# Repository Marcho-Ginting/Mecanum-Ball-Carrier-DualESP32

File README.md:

# Mecanum-Ball-Carrier-DualESP32

A high-performance mechatronic system utilizing omnidirectional locomotion and a distributed processing architecture for precision robotics tasks.

## 📊 Technical Specifications
* **Architecture:** Dual-ESP32 System (Distributed processing for control and feedback).
* **Locomotion:** 4-wheel drive using Mecanum wheels for 360-degree holonomic movement.
* **Actuation:** 4x High-torque Direct Drive actuators with integrated encoders.
* **PCB:** Custom-manufactured board for power distribution and encoder signal conditioning.

## ⚡ Engineering Highlights
* **Distributed Processing:** Implemented a Dual-ESP32 architecture to isolate real-time motor control and encoder processing from higher-level telemetry and communication, ensuring system stability.
* **Precision Motion Control:** Developed algorithms for Mecanum wheel kinematics, utilizing closed-loop encoder feedback to achieve high-precision velocity and positional tracking.
* **System Integration:** Engineered a custom PCB to consolidate four motor drivers and encoder inputs, optimizing signal integrity and reducing the mechanical footprint of the electronics.
* **Leadership:** Led a cross-disciplinary team of engineers, managing the full development lifecycle from component selection to final system debugging.

## 📂 Repository Structure
* `/logic`: Main logic digital board
* `/pdb`: Driver motor and power distribution board.

## 📷 3D KiCad Render Images

<table style="width:100%">
  <tr>
    <td align="center">
      <br/>
      <b>PDB</b>
    </td>
    <td align="center">
      <br/>
      <b>Logic</b>
    </td>
  </tr>
</table>

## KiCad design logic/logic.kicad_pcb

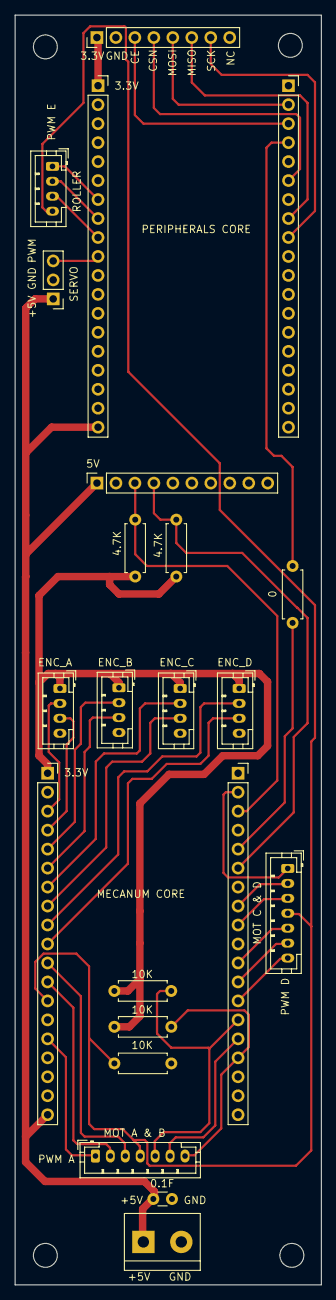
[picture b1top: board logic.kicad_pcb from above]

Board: 2 copper layers, 41.0 x 170.0 mm, 22 parts (0 on the bottom side), 38 nets.

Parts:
C_BYPASS1: 0.1uF; C_Disc_D3.0mm_W1.6mm_P2.50mm
J_DRV_SIG1, J_DRV_SIG2: Conn_01x07; JST_PH_B7B-PH-K_1x07_P2.00mm_Vertical
J_DRV_SIG_1: Conn_01x04; JST_PH_B4B-PH-K_1x04_P2.00mm_Vertical
J_IMU1: Conn_01x10_Socket; PinSocket_1x10_P2.54mm_Vertical
J_LEFT_ENC1, J_LEFT_ENC2: Conn_01x04; JST_PH_B4B-PH-K_1x04_P2.00mm_Vertical
J_LEFT_HEADERS1, J_LEFT_HEADERS2: Conn_01x19_Pin; PinSocket_1x19_P2.54mm_Vertical
J_LOGIC1: Screw_Terminal_01x02; TerminalBlock_bornier-2_P5.08mm
J_RF1: Conn_01x08_Pin; PinHeader_1x08_P2.54mm_Vertical
J_RIGHT_ENC1, J_RIGHT_ENC2: Conn_01x04; JST_PH_B4B-PH-K_1x04_P2.00mm_Vertical
J_RIGHT_HEADERS1, J_RIGHT_HEADERS2: Conn_01x19_Pin; PinSocket_1x19_P2.54mm_Vertical
J_SERVO1: Conn_01x03_Pin; PinHeader_1x03_P2.54mm_Vertical
R_JUMPER1: 0; R_Axial_DIN0207_L6.3mm_D2.5mm_P7.62mm_Horizontal
R_PULLUP1, R_PULLUP2: 4.7K; R_Axial_DIN0207_L6.3mm_D2.5mm_P7.62mm_Horizontal
R_PULLUP3, R_PULLUP4, R_PULLUP5: 10K; R_Axial_DIN0207_L6.3mm_D2.5mm_P7.62mm_Horizontal

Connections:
/3.3V_MEC: J_LEFT_ENC1.1, J_LEFT_ENC2.1, J_LEFT_HEADERS1.1, J_RIGHT_ENC1.1, J_RIGHT_ENC2.1, R_PULLUP1.2, R_PULLUP2.2, R_PULLUP3.2, R_PULLUP5.2
/3.3V_PER: J_LEFT_HEADERS2.1, J_RF1.1
/+5V: C_BYPASS1.1, J_IMU1.1, J_LEFT_HEADERS1.19, J_LEFT_HEADERS2.19, J_LOGIC1.1, J_SERVO1.1
/CE: J_RF1.3, J_RIGHT_HEADERS2.3
/CSN: J_RF1.4, J_RIGHT_HEADERS2.6
/ENC_A1: J_LEFT_ENC1.2, J_LEFT_HEADERS1.3
/ENC_A2: J_LEFT_ENC1.3, J_LEFT_HEADERS1.4
/ENC_B1: J_LEFT_ENC2.2, J_LEFT_HEADERS1.5
/ENC_B2: J_LEFT_ENC2.3, J_LEFT_HEADERS1.6
/ENC_C1: J_LEFT_HEADERS1.7, J_RIGHT_ENC1.2
/ENC_C2: J_LEFT_HEADERS1.8, J_RIGHT_ENC1.3
/ENC_D1: J_LEFT_HEADERS1.9, J_RIGHT_ENC2.2
/ENC_D2: J_LEFT_HEADERS1.10, J_RIGHT_ENC2.3
/GND_LOGIC: C_BYPASS1.2, J_IMU1.2, J_LEFT_ENC1.4, J_LEFT_ENC2.4, J_LEFT_HEADERS1.14, J_LEFT_HEADERS2.14, J_LOGIC1.2, J_RF1.2, J_RIGHT_ENC1.4, J_RIGHT_ENC2.4, J_RIGHT_HEADERS1.1, J_RIGHT_HEADERS2.1, J_SERVO1.2, R_PULLUP4.2
/IN_A1: J_DRV_SIG1.3, J_LEFT_HEADERS1.11
/IN_A2: J_DRV_SIG1.2, J_LEFT_HEADERS1.12
/IN_B1: J_DRV_SIG1.5, J_RIGHT_HEADERS1.14, R_PULLUP3.1
/IN_B2: J_DRV_SIG1.6, J_RIGHT_HEADERS1.15
/IN_C1: J_DRV_SIG2.3, J_RIGHT_HEADERS1.9
/IN_C2: J_DRV_SIG2.2, J_RIGHT_HEADERS1.8
/IN_D1: J_DRV_SIG2.5, J_RIGHT_HEADERS1.11
/IN_D2: J_DRV_SIG2.6, J_RIGHT_HEADERS1.12
/IN_E1: J_DRV_SIG_1.3, J_LEFT_HEADERS2.9
/IN_E2: J_DRV_SIG_1.2, J_LEFT_HEADERS2.8
/MISO: J_RF1.6, J_RIGHT_HEADERS2.8
/MOSI: J_RF1.5, J_RIGHT_HEADERS2.2
/PWM_A: J_DRV_SIG1.1, J_LEFT_HEADERS1.15
/PWM_B: J_DRV_SIG1.7, J_RIGHT_HEADERS1.16, R_PULLUP5.1
/PWM_C: J_DRV_SIG2.1, J_RIGHT_HEADERS1.2
/PWM_D: J_DRV_SIG2.7, J_RIGHT_HEADERS1.13
/PWM_E: J_DRV_SIG_1.1, J_LEFT_HEADERS2.7
/PWM_SERVO: J_LEFT_HEADERS2.10, J_SERVO1.3
/SCK: J_RF1.7, J_RIGHT_HEADERS2.9
/SCL: J_IMU1.3, J_RIGHT_HEADERS1.3, R_PULLUP2.1
/SDA: J_IMU1.4, J_RIGHT_HEADERS1.6, R_PULLUP1.1
/STBY: J_DRV_SIG1.4, J_DRV_SIG2.4, J_DRV_SIG_1.4, J_LEFT_HEADERS1.13, R_PULLUP4.1
/UART_MASTER: J_RIGHT_HEADERS2.4, R_JUMPER1.1
/UART_SLAVE: J_RIGHT_HEADERS1.5, R_JUMPER1.2

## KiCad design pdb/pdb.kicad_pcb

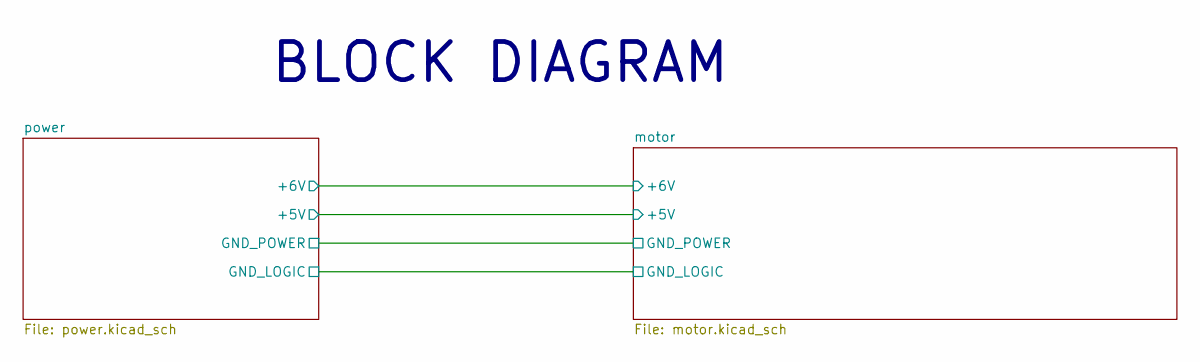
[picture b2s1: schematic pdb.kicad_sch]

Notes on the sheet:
BLOCK DIAGRAM

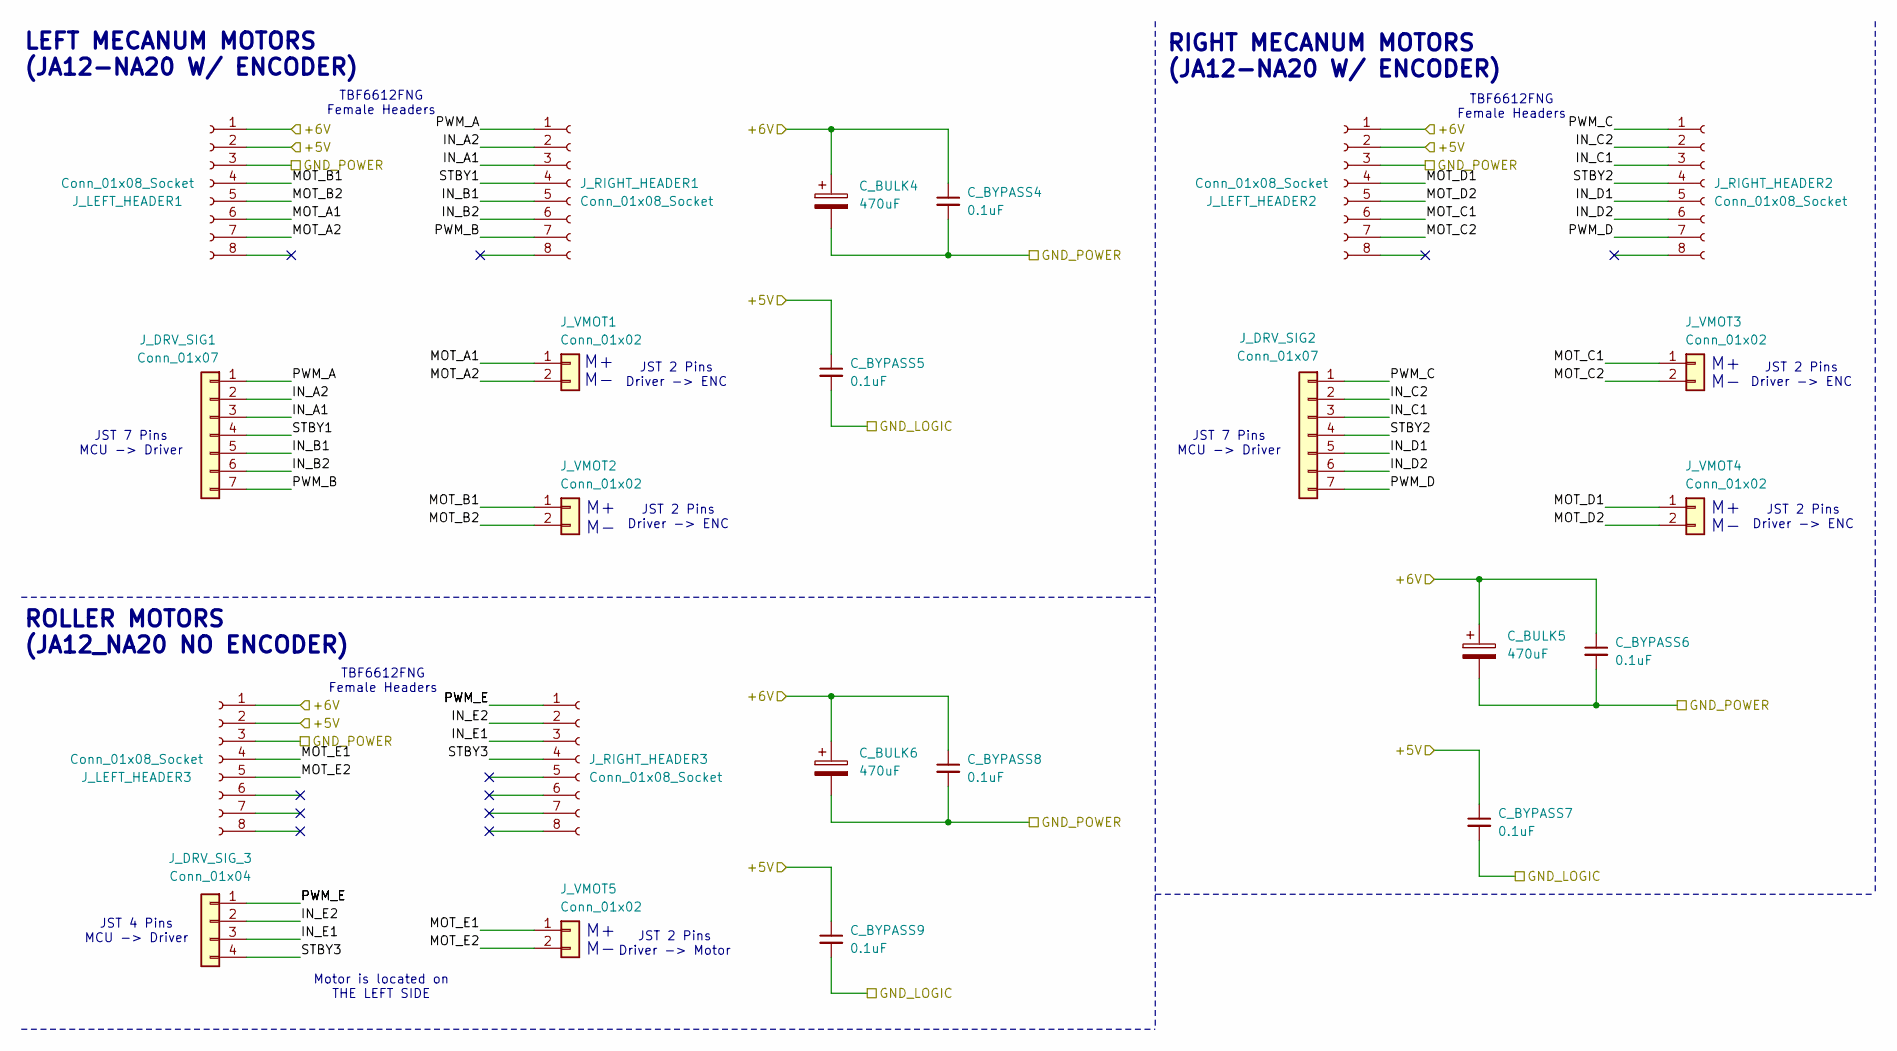
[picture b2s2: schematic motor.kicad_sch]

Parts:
C_BULK4, C_BULK5, C_BULK6: 470uF; CP_Radial_D10.0mm_P5.00mm
C_BYPASS4, C_BYPASS5, C_BYPASS6, C_BYPASS7, C_BYPASS8, C_BYPASS9: 0.1uF; C_Disc_D3.0mm_W1.6mm_P2.50mm
J_DRV_SIG1, J_DRV_SIG2: Conn_01x07; JST_PH_B7B-PH-K_1x07_P2.00mm_Vertical
J_DRV_SIG_3: Conn_01x04; JST_PH_B4B-PH-K_1x04_P2.00mm_Vertical
J_LEFT_HEADER1, J_LEFT_HEADER2, J_LEFT_HEADER3: Conn_01x08_Socket; PinSocket_1x08_P2.54mm_Vertical
J_RIGHT_HEADER1, J_RIGHT_HEADER2, J_RIGHT_HEADER3: Conn_01x08_Socket; PinSocket_1x08_P2.54mm_Vertical
J_VMOT1, J_VMOT2, J_VMOT3, J_VMOT4, J_VMOT5: Conn_01x02; JST_PH_B2B-PH-K_1x02_P2.00mm_Vertical

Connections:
/motor/+5V: C_BYPASS5.1, C_BYPASS7.1, C_BYPASS9.1, J_LEFT_HEADER1.2, J_LEFT_HEADER2.2, J_LEFT_HEADER3.2; also elsewhere on the board
/motor/+6V: C_BULK4.1, C_BULK5.1, C_BULK6.1, C_BYPASS4.1, C_BYPASS6.1, C_BYPASS8.1, J_LEFT_HEADER1.1, J_LEFT_HEADER2.1, J_LEFT_HEADER3.1; also elsewhere on the board
/motor/GND_LOGIC: C_BYPASS5.2, C_BYPASS7.2, C_BYPASS9.2; also elsewhere on the board
/motor/GND_POWER: C_BULK4.2, C_BULK5.2, C_BULK6.2, C_BYPASS4.2, C_BYPASS6.2, C_BYPASS8.2, J_LEFT_HEADER1.3, J_LEFT_HEADER2.3, J_LEFT_HEADER3.3; also elsewhere on the board
/motor/IN_A1: J_DRV_SIG1.3, J_RIGHT_HEADER1.3
/motor/IN_A2: J_DRV_SIG1.2, J_RIGHT_HEADER1.2
/motor/IN_B1: J_DRV_SIG1.5, J_RIGHT_HEADER1.5
/motor/IN_B2: J_DRV_SIG1.6, J_RIGHT_HEADER1.6
/motor/IN_C1: J_DRV_SIG2.3, J_RIGHT_HEADER2.3
/motor/IN_C2: J_DRV_SIG2.2, J_RIGHT_HEADER2.2
/motor/IN_D1: J_DRV_SIG2.5, J_RIGHT_HEADER2.5
/motor/IN_D2: J_DRV_SIG2.6, J_RIGHT_HEADER2.6
/motor/IN_E1: J_DRV_SIG_3.3, J_RIGHT_HEADER3.3
/motor/IN_E2: J_DRV_SIG_3.2, J_RIGHT_HEADER3.2
/motor/MOT_A1: J_LEFT_HEADER1.6, J_VMOT1.1
/motor/MOT_A2: J_LEFT_HEADER1.7, J_VMOT1.2
/motor/MOT_B1: J_LEFT_HEADER1.4, J_VMOT2.1
/motor/MOT_B2: J_LEFT_HEADER1.5, J_VMOT2.2
/motor/MOT_C1: J_LEFT_HEADER2.6, J_VMOT3.1
/motor/MOT_C2: J_LEFT_HEADER2.7, J_VMOT3.2
/motor/MOT_D1: J_LEFT_HEADER2.4, J_VMOT4.1
/motor/MOT_D2: J_LEFT_HEADER2.5, J_VMOT4.2
/motor/MOT_E1: J_LEFT_HEADER3.4, J_VMOT5.1
/motor/MOT_E2: J_LEFT_HEADER3.5, J_VMOT5.2
/motor/PWM_A: J_DRV_SIG1.1, J_RIGHT_HEADER1.1
/motor/PWM_B: J_DRV_SIG1.7, J_RIGHT_HEADER1.7
/motor/PWM_C: J_DRV_SIG2.1, J_RIGHT_HEADER2.1
/motor/PWM_D: J_DRV_SIG2.7, J_RIGHT_HEADER2.7
/motor/PWM_E: J_DRV_SIG_3.1, J_RIGHT_HEADER3.1
/motor/STBY1: J_DRV_SIG1.4, J_RIGHT_HEADER1.4
/motor/STBY2: J_DRV_SIG2.4, J_RIGHT_HEADER2.4
/motor/STBY3: J_DRV_SIG_3.4, J_RIGHT_HEADER3.4

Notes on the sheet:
ROLLER MOTORS (JA12_NA20 NO ENCODER)
JST 2 Pins Driver -> ENC
LEFT MECANUM MOTORS (JA12-NA20 W/ ENCODER)
JST 7 Pins MCU -> Driver
TBF6612FNG Female Headers
JST 2 Pins Driver -> Motor
JST 4 Pins MCU -> Driver
RIGHT MECANUM MOTORS (JA12-NA20 W/ ENCODER)
Motor is located on THE LEFT SIDE

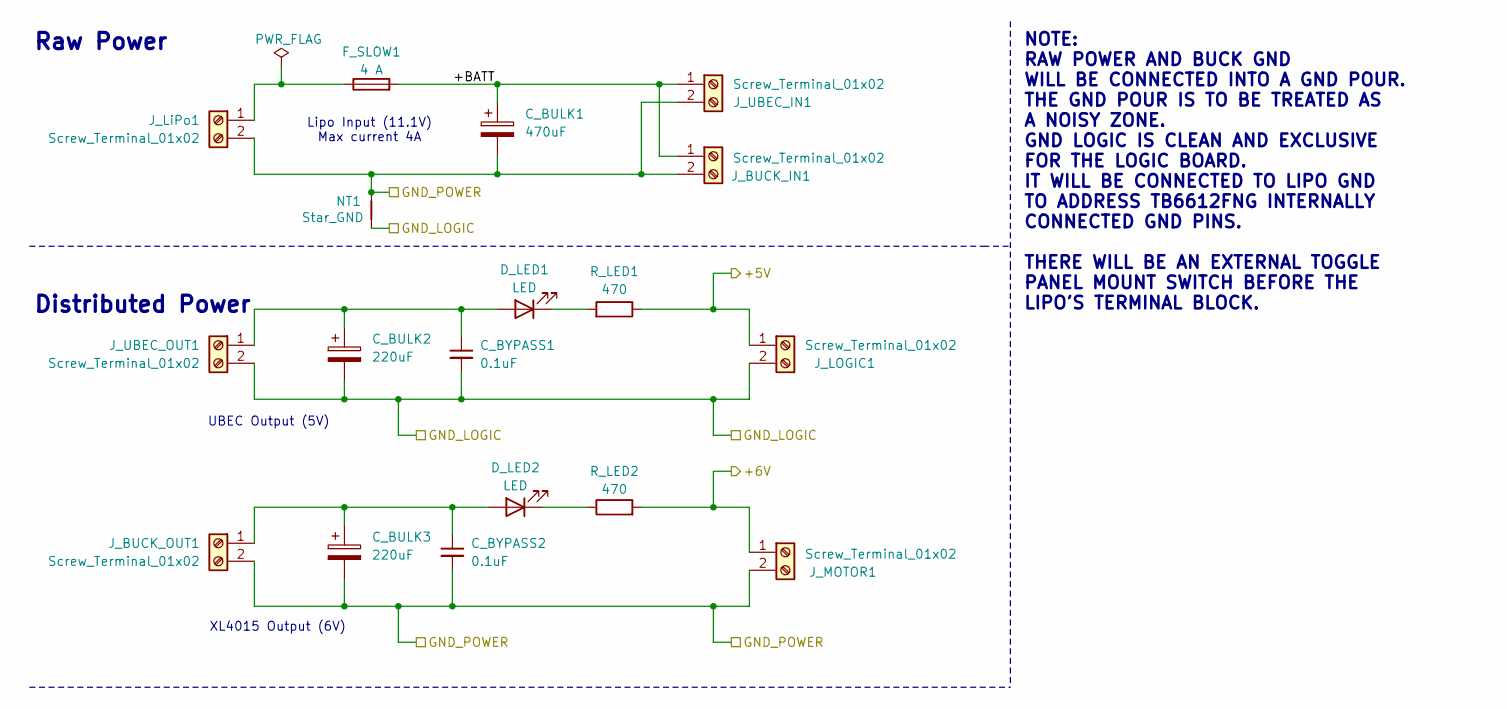
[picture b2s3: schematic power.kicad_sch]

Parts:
C_BULK1: 470uF; CP_Radial_D10.0mm_P5.00mm
C_BULK2, C_BULK3: 220uF; CP_Radial_D8.0mm_P3.50mm
C_BYPASS1, C_BYPASS2: 0.1uF; C_Disc_D3.0mm_W1.6mm_P2.50mm
D_LED1, D_LED2: LED; LED_D5.0mm_Clear
F_SLOW1: 4 A; Fuseholder_Clip-5x20mm_Bel_FC-203-22_Lateral_P17.80x5.00mm_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
J_BUCK_IN1: Screw_Terminal_01x02; TerminalBlock_bornier-2_P5.08mm
J_BUCK_OUT1: Screw_Terminal_01x02; TerminalBlock_bornier-2_P5.08mm
J_LOGIC1: Screw_Terminal_01x02; TerminalBlock_bornier-2_P5.08mm
J_LiPo1: Screw_Terminal_01x02; TerminalBlock_MetzConnect_Type175_RT02702HBLC_1x02_P7.50mm_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
J_MOTOR1: Screw_Terminal_01x02; TerminalBlock_bornier-2_P5.08mm
J_UBEC_IN1: Screw_Terminal_01x02; TerminalBlock_bornier-2_P5.08mm
J_UBEC_OUT1: Screw_Terminal_01x02; TerminalBlock_bornier-2_P5.08mm
NT1: Star_GND; NetTie-2_THT_Pad1.0mm
R_LED1, R_LED2: 470; R_Axial_DIN0207_L6.3mm_D2.5mm_P7.62mm_Horizontal

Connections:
/motor/+5V: J_LOGIC1.1, R_LED1.1; also elsewhere on the board
/motor/+6V: J_MOTOR1.1, R_LED2.2; also elsewhere on the board
/motor/GND_LOGIC: C_BULK2.2, C_BYPASS1.2, J_LOGIC1.2, J_UBEC_OUT1.2, NT1.1; also elsewhere on the board
/motor/GND_POWER: C_BULK1.2, C_BULK3.2, C_BYPASS2.2, J_BUCK_IN1.2, J_BUCK_OUT1.2, J_LiPo1.2, J_MOTOR1.2, J_UBEC_IN1.2, NT1.2; also elsewhere on the board
/power/+BATT: C_BULK1.1, F_SLOW1.2, J_BUCK_IN1.1, J_UBEC_IN1.1
unnamed: C_BULK2.1, C_BYPASS1.1, D_LED1.2 (A), J_UBEC_OUT1.1
unnamed: D_LED1.1 (K), R_LED1.2
unnamed: C_BULK3.1, C_BYPASS2.1, D_LED2.2 (A), J_BUCK_OUT1.1
unnamed: D_LED2.1 (K), R_LED2.1
unnamed: F_SLOW1.1, J_LiPo1.1

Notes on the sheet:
NOTE: RAW POWER AND BUCK GND WILL BE CONNECTED INTO A GND POUR. THE GND POUR IS TO BE TREATED AS A NOISY ZONE. GND LOGIC IS CLEAN AND EXCLUSIVE FOR THE LOGIC BOARD. IT WILL BE CONNECTED TO LIPO GND TO ADDRESS TB6612FNG INTERNALLY CONNECTED GND PINS. THERE WILL BE AN EXTERNAL TOGGLE PANEL MOUNT SWIT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
UBEC Output (5V)
Raw Power
XL4015 Output (6V)
Distributed Power
Lipo Input (11.1V) Max current 4A

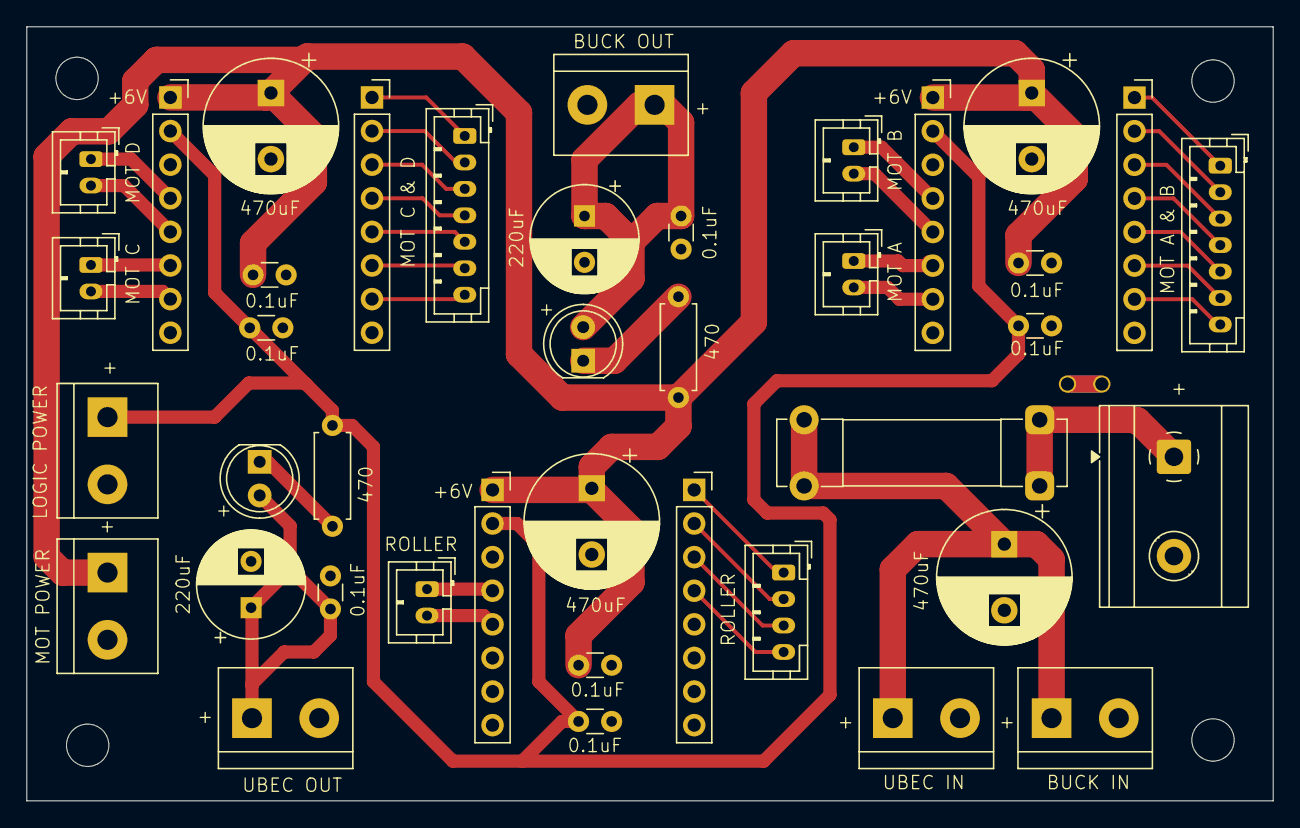
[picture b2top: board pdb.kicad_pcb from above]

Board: 2 copper layers, 94.2 x 58.5 mm, 41 parts (0 on the bottom side), 38 nets.
